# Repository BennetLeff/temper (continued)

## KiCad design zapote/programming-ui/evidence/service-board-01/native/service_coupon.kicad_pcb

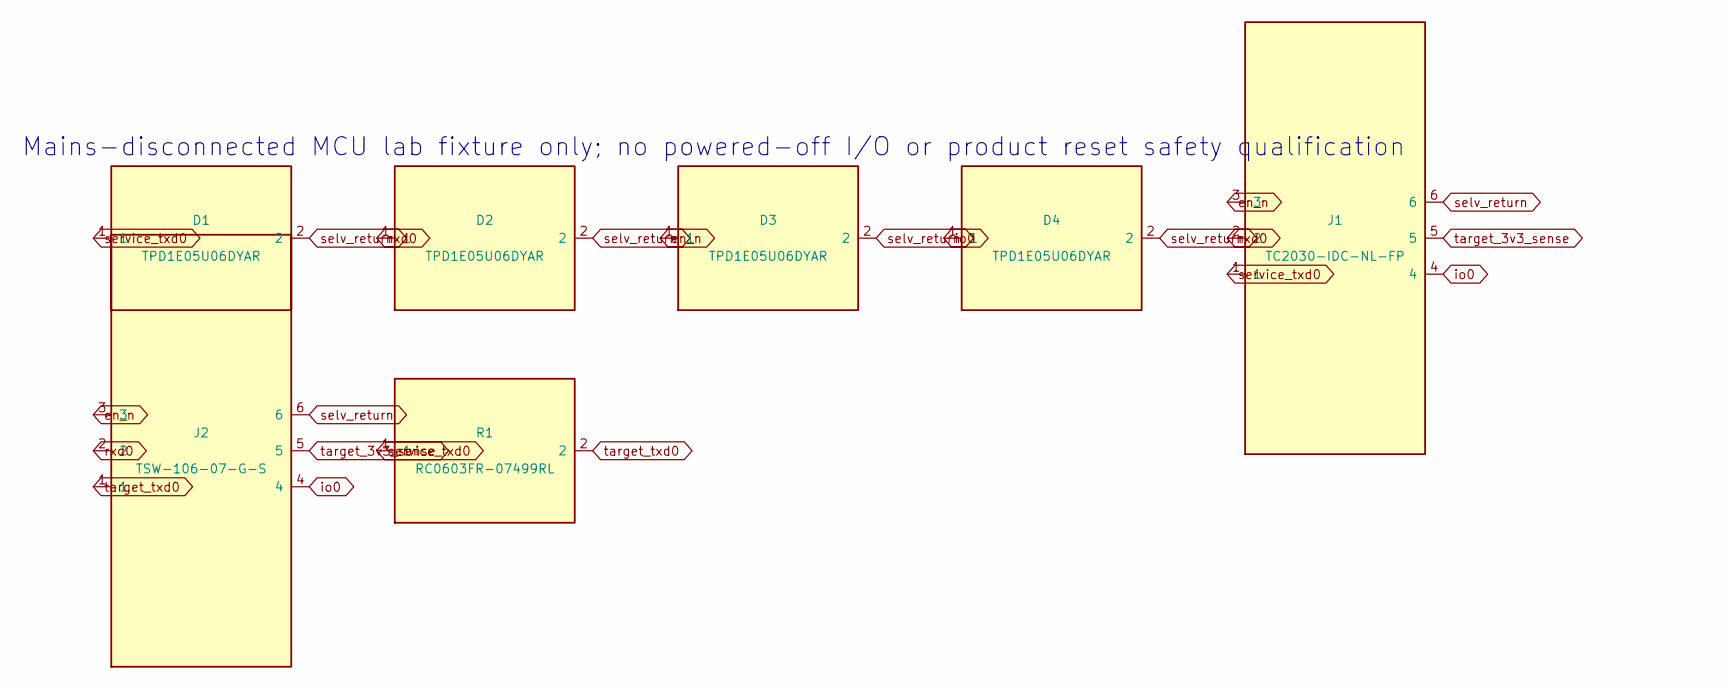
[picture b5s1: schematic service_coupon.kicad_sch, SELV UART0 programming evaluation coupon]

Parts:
D1, D2, D3, D4: TPD1E05U06DYAR; D_SOD-523
J1: TC2030-IDC-NL-FP; Tag-Connect_TC2030-IDC-NL_2x03_P1.27mm_Vertical
J2: TSW-106-07-G-S; PinHeader_1x06_P2.54mm_Vertical
R1: RC0603FR-07499RL; R_0603_1608Metric

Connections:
en_n: D3.1, J1.3, J2.3
io0: D4.1, J1.4, J2.4
rxd0: D2.1, J1.2, J2.2
selv_return: D1.2, D2.2, D3.2, D4.2, J1.6, J2.6
service_txd0: D1.1, J1.1, R1.1
target_3v3_sense: J1.5, J2.5
target_txd0: J2.1, R1.2

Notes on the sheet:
Mains-disconnected MCU lab fixture only; no powered-off I/O or product reset safety qualification

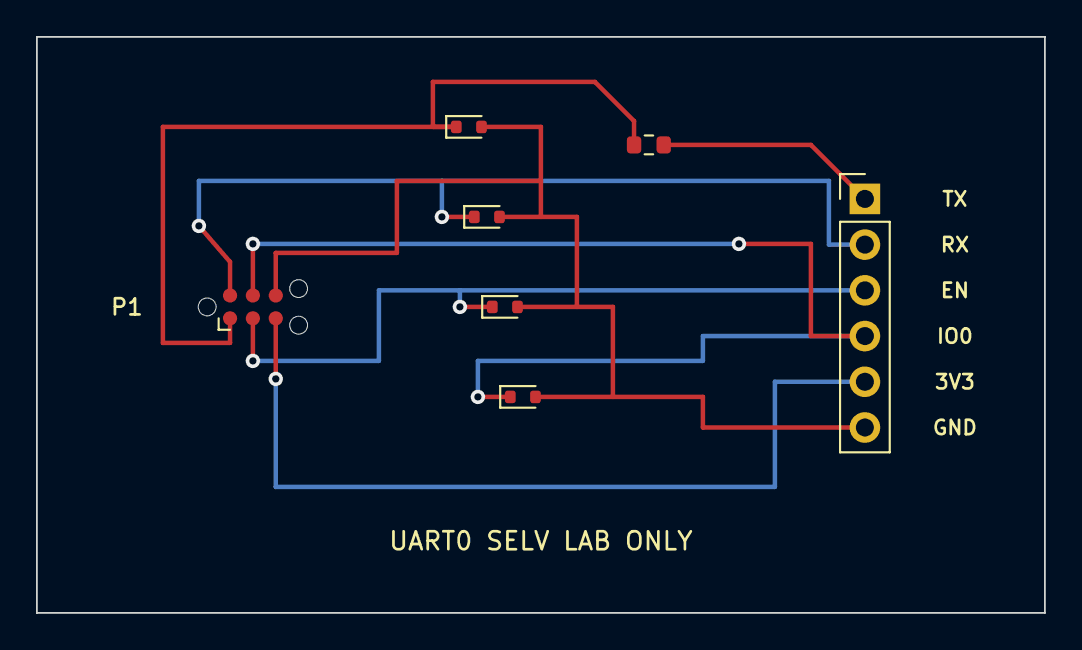
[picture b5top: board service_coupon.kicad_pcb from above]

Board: 6 copper layers, 56.0 x 32.0 mm, 7 parts (0 on the bottom side), 7 nets.
